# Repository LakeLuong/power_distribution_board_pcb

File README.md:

# power_distribution_board_pcb
Custom KiCad power distribution PCB that takes in +48V and regulates it down to 5V, 3.3V and 12V through two adjustable Lm760660 buck converters and a Tps62913. I made this for a bigger project I am working on for an underwater FPV drone to power different components such as ESCs which will take in +48V, sensors which takes 3.3V and 5V for my raspberry pi, and 12V for cameras. 

BOM: 

Tps62913	Low current buck converter converting 5V to 3.3V	2	$5.52		

Lm70660	High Current Buck Converter that takes 48V and brings it down to 12V and 5V	2	$13.60		

0805 4mOhm resistors	Current-sense resistors	10	$5.57	

0805 54.9k Ohm resistors	resistor connects from RT to AGND, helps with switching frequency	10	$0.37	

0806 20.5kOhm resistors	En Vulo resistors	10	$0.34	

0805 3.24kOhm resistor	Compensation capacitor for lm760660	10	$0.34	

0805 1 Ohm resistor	Bootstrap resistor	10	$0.51

0805 2.49kOhm resistor	feedback divider resistor	10	$0.34	

0805 4.87kOhm resistor	Feedback divider resistor	10	$0.34		

0805 52.3kOhm resistor	S-CONF resistor	10	$0.34	

0805 31.6kOhm resistor	Resistor divider for feedback	10	$0.58	

0805 100kOhm resistor	UVLO resistor, pull up resistors, etc, to control current flow	25	$0.64		

2.2uH inductor	Stores energy during switching and smooths current	3	$6.61	

Ferrite Bead	Blocks high frequency noise	5	$1.55	

0805 470nF Ceramic Capacitor	Reduce low frequency output noise on the Tps62913	10	$1.24	

0806 0.1uF Ceramic Capacitor	High frequency bypass capacitors	10	$1.07

0805 0.1uF Ceramic Capacitor	Decouples VDDA analog bias rail	10	$0.72	

0805 4.7uF Ceramic Capacitor	bypass/decoupling capacitor for VCC	5	$1.60	

0805 22uf Ceramic Capacitor	Smooths output voltage	10	$3.74	

1210 47uF Ceramic Capacitors	Smooths output voltage from regulator	15	$8.42	

0805 10uF Ceramic Capacitors	Input capacitors to provide short bursts of current to regulator	10	$3.48		

1210 4.7 uF Ceramic Capacitors	Input capacitors to provide short burst of current	10	$8.49		

0805 150pf Ceramic Capacitors	Compensation capacitors, helps buck converter stay stable from high frequency noise	10	$0.85		

1210 22uF Ceramic Capacitor	Gives high frequency noise to GND	10	$4.77

0805 10nF Ceramice Capacitors	bypass and filtering + provide positive power supply through VCC	10	$0.60	

0805 0.047 uF Ceramic Capacitor	Boostrap capacitor for buck converter	10	$1.47	

0805 2200pF SMD Ceramic Capacitor	Decoupling and filtering for 5v rail	10	$0.39

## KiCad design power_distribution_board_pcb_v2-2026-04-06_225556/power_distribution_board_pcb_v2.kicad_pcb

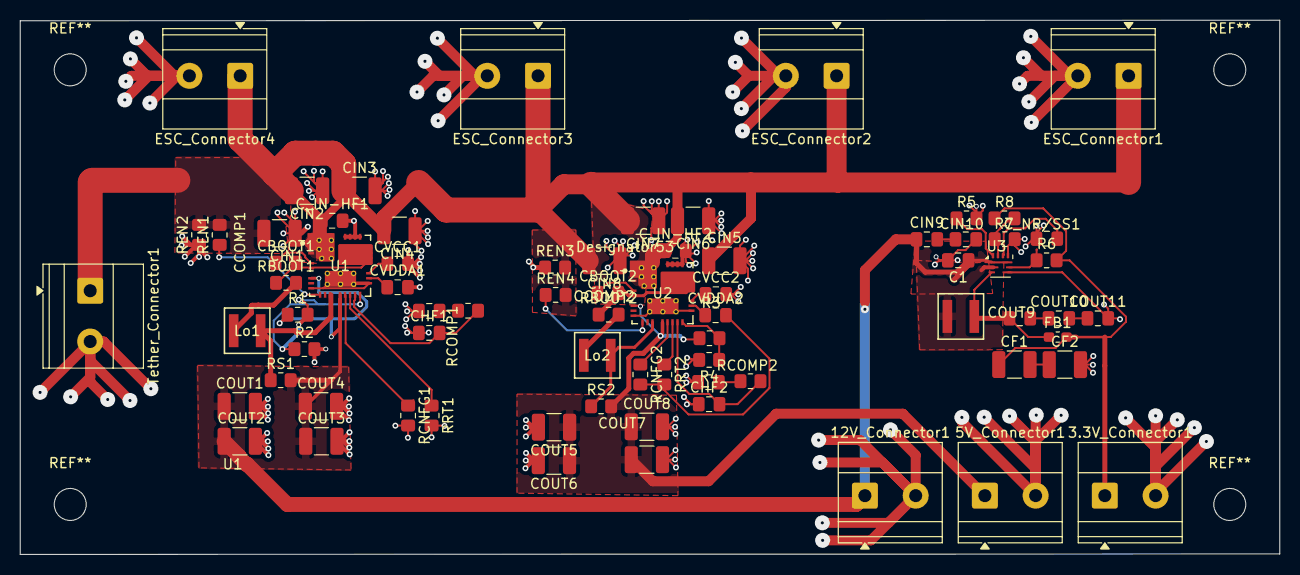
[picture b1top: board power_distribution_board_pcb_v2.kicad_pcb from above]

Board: 2 copper layers, 126.0 x 53.4 mm, 74 parts (0 on the bottom side), 40 nets.

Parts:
3.3V_Connector1, 5V_Connector1, 12V_Connector1: Conn_01x02; TerminalBlock_Phoenix_MKDS-1,5-2-5.08_1x02_P5.08mm_Horizont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
C1: 2.2nF; C_0805_2012Metric_Pad1.18x1.45mm_HandSolder
CBOOT1: 47nF; C_0805_2012Metric_Pad1.18x1.45mm_HandSolder
CBOOT2: 4.7; C_0805_2012Metric_Pad1.18x1.45mm_HandSolder
CCOMP1, CCOMP2: 10nF; C_0805_2012Metric_Pad1.18x1.45mm_HandSolder
CF1, CF2: 22uF; C_1210_3225Metric_Pad1.33x2.70mm_HandSolder
CHF1, CHF2: 150pF; C_0805_2012Metric_Pad1.18x1.45mm_HandSolder
CIN1, CIN2, CIN3, CIN4, CIN5, CIN6, CIN7, CIN8: 4.7µF; C_1210_3225Metric_Pad1.33x2.70mm_HandSolder
CIN9, CIN10: 10uF; C_0805_2012Metric_Pad1.18x1.45mm_HandSolder
COUT1, COUT2, COUT3, COUT4: 47uF; C_1210_3225Metric_Pad1.33x2.70mm_HandSolder
COUT5, COUT6, COUT7, COUT8: 47; C_1210_3225Metric_Pad1.33x2.70mm_HandSolder
COUT9, COUT10, COUT11: 22uF; C_0805_2012Metric_Pad1.18x1.45mm_HandSolder
CVCC1: 4.7uF; C_0805_2012Metric_Pad1.18x1.45mm_HandSolder
CVCC2: 4.7; C_0805_2012Metric_Pad1.18x1.45mm_HandSolder
CVDDA1: 0.1uF; C_0805_2012Metric_Pad1.18x1.45mm_HandSolder
CVDDA2: 0.1; C_0805_2012Metric_Pad1.18x1.45mm_HandSolder
C_IN-HF1, C_IN-HF2: 0.1 µF; C_0805_2012Metric_Pad1.18x1.45mm_HandSolder
C_NR/SS1: 470nF; C_0805_2012Metric_Pad1.18x1.45mm_HandSolder
ESC_Connector1, ESC_Connector2, ESC_Connector3, ESC_Connector4: Conn_01x02; TerminalBlock_Phoenix_MKDS-1,5-2-5.08_1x02_P5.08mm_Horizont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
FB1: FerriteBead; L_0603_1608Metric_Pad1.05x0.95mm_HandSolder
L1: 2.2uH; IND_XGL4030_COC-M
Lo1: 2.2uH; IND_XGL4030_COC-M
Lo2: 3.3; IND_XGL4030_COC-M
R1: 100kF; R_0805_2012Metric_Pad1.20x1.40mm_HandSolder
R2: 31.6kF; R_0805_2012Metric_Pad1.20x1.40mm_HandSolder
R3, R6: 100k; R_0805_2012Metric_Pad1.20x1.40mm_HandSolder
R4: 31.6k; R_0805_2012Metric_Pad1.20x1.40mm_HandSolder
R5: 52.3k; R_0805_2012Metric_Pad1.20x1.40mm_HandSolder
R7: 4.87k; R_0805_2012Metric_Pad1.20x1.40mm_HandSolder
R8: 2.49k; R_0805_2012Metric_Pad1.20x1.40mm_HandSolder
RBOOT1, RBOOT2: 1Ohm; R_0805_2012Metric_Pad1.20x1.40mm_HandSolder
RCNFG1, RCNFG2: 29.4K; R_0805_2012Metric_Pad1.20x1.40mm_HandSolder
RCOMP1: 3.24kF; R_0805_2012Metric_Pad1.20x1.40mm_HandSolder
RCOMP2: 3.24k; R_0805_2012Metric_Pad1.20x1.40mm_HandSolder
REN1, REN4: 100k; R_0805_2012Metric_Pad1.20x1.40mm_HandSolder
REN2, REN3: 20.5k; R_0805_2012Metric_Pad1.20x1.40mm_HandSolder
RRT1: 54.9K; R_0805_2012Metric_Pad1.20x1.40mm_HandSolder
RRT2: R; R_0805_2012Metric_Pad1.20x1.40mm_HandSolder
RS1: 4mQ; R_0805_2012Metric_Pad1.20x1.40mm_HandSolder
RS2: 5m; R_0805_2012Metric_Pad1.20x1.40mm_HandSolder
Tether_Connector1: Conn_01x02; TerminalBlock_Phoenix_MKDS-1,5-2-5.08_1x02_P5.08mm_Horizont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
U1, U2: LM70660RRXR; RRX0029B-MFG
U3: TPS62913; Texas_RPU0010A_VQFN-HR-10_2x2mm_P0.5mm

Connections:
+48V: CIN1.2, CIN2.2, CIN3.1, CIN4.2, CIN5.1, CIN6.2, CIN7.2, CIN8.2, C_IN-HF1.1, C_IN-HF2.1, ESC_Connector1.1, ESC_Connector2.1, ESC_Connector3.1, ESC_Connector4.1, REN1.2, REN2.2, REN3.2, REN4.2, Tether_Connector1.1, U1.1 (VIN4), U1.2 (VIN5), U1.3 (VIN6), U1.27 (VIN1), U1.28 (VIN2), U1.29 (VIN3), U1.37, U1.38, U1.39, U1.40, U1.41, U1.42, U2.1 (VIN4), U2.2 (VIN5), U2.3 (VIN6), U2.27 (VIN1), U2.28 (VIN2), U2.29 (VIN3), U2.37, U2.38, U2.39, U2.40, U2.41
/3.3V_BUS: 3.3V_Connector1.1, CF1.1, FB1.2, R6.2, R8.1
/5V_BUS: 5V_Connector1.1, COUT5.1, COUT6.1, COUT7.1, COUT8.1, R3.1, RS2.2, U2.6 (BIAS), U2.12 (VOUT)
/12V_BUS: 12V_Connector1.1, C1.1, CIN9.1, COUT1.1, COUT2.1, COUT3.1, COUT4.1, R1.1, RS1.2, U1.6 (BIAS), U1.12 (VOUT), U3.1 (EN/SYNC), U3.6 (VIN)
/AGND: CVDDA2.2, RCNFG2.2, RRT2.2
/CONFIG: RCNFG2.1, U2.13 (CONFIG)
/CONFIG_12V: RCNFG1.1, U1.13 (CONFIG)
/EN_UVLO: REN4.1, U2.9 (EN_UVLO)
/EN_UVLO_12V: REN1.1, U1.9 (EN_UVLO)
/EXTCOMP: CHF2.2, RCOMP2.2, U2.15 (EXTCOMP)
/EXTCOMP_12V: CHF1.2, RCOMP1.2, U1.15 (EXTCOMP)
/FB_5V: R3.2, R4.1, U2.16 (FB)
/FB_12V: R1.2, R2.1, U1.16 (FB)
/NR/SS: C_NR/SS1.2, U3.8 (NR/SS)
/RT: RRT2.1, U2.14 (RT)
/RT_12V: RRT1.1, U1.14 (RT)
/VDDA: CVDDA2.1, U2.18 (VDDA)
/VDDA_12V: CVDDA1.1, U1.18 (VDDA)
GND: 3.3V_Connector1.2, 5V_Connector1.2, 12V_Connector1.2, C1.2, CCOMP1.1, CCOMP2.1, CF2.2, CHF1.1, CHF2.1, CIN1.1, CIN2.1, CIN3.2, CIN4.1, CIN5.2, CIN6.1, CIN7.1, CIN8.1, CIN10.2, COUT1.2, COUT2.2, COUT3.2, COUT4.2, COUT5.2, COUT6.2, COUT7.2, COUT8.2, COUT11.2, CVCC1.2, CVCC2.2, CVDDA1.2, C_IN-HF1.2, C_IN-HF2.2, C_NR/SS1.1, ESC_Connector1.2, ESC_Connector2.2, ESC_Connector3.2, ESC_Connector4.2, R2.2, R4.2, R5.2, R7.2, RCNFG1.2, REN2.1, REN3.1, RRT1.2, Tether_Connector1.2, U1.8 (PFM_SYNCIN), U1.17 (AGND), U1.23 (PGND1), U1.24 (PGND2), U1.25 (PGND3), U1.26 (PGND4), U1.30 (PGND), U1.31, U1.32, U1.33, U1.34, U1.35, U1.36, U2.8 (PFM_SYNCIN), U2.17 (AGND), U2.23 (PGND1), U2.24 (PGND2), U2.25 (PGND3), U2.26 (PGND4), U2.30 (PGND), U2.31, U2.32, U2.33, U2.34, U2.35, U2.36, U3.4 (PGND), U3.7 (PSNS)
unnamed: CCOMP1.2, RCOMP1.1
unnamed: CCOMP2.2, RCOMP2.1
unnamed: CF1.2, CF2.1
unnamed: CIN9.2, CIN10.1
unnamed: COUT9.2, COUT10.1
unnamed: COUT10.2, COUT11.1
unnamed: Lo1.1, RBOOT1.2
unnamed: Lo2.1, RBOOT2.2
unnamed: CBOOT1.1, U1.4 (CBOOT)
unnamed: Lo1.2, RS1.1, U1.11 (ISNS+)
unnamed: CBOOT1.2, RBOOT1.1, U1.5 (SW4), U1.20 (SW1), U1.21 (SW2), U1.22 (SW3)
unnamed: CVCC1.1, U1.19 (VCC)
unnamed: CBOOT2.1, U2.4 (CBOOT)
unnamed: Lo2.2, RS2.1, U2.11 (ISNS+)
unnamed: CBOOT2.2, RBOOT2.1, U2.5 (SW4), U2.20 (SW1), U2.21 (SW2), U2.22 (SW3)
unnamed: CVCC2.1, U2.19 (VCC)
unnamed: R7.1, R8.2, U3.9 (FB)
unnamed: R6.1, U3.5 (PG)
unnamed: R5.1, U3.10 (S-CONF)
unnamed: L1.1, U3.2 (SW)
unnamed: COUT9.1, FB1.1, L1.2, U3.3 (VO)

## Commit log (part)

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2026-03-28 Added buck converter datasheet
2026-03-30 Added new datasheet for low noise voltage regulator
2026-04-01 added schematic and footprint
2026-04-03 Added project files
2026-04-07 Added version 2 of the pcb schematic
2026-06-03 Update KiCad project files
2026-06-03 moved files
2026-06-03 Revise README description for power distribution PCB
    Updated project description to specify input voltage and output regulation details.
2026-06-03 Update README with project application details
    Expanded project description to include application details for underwater FPV drone.
2026-06-03 Update README with project image
    Added an image to the README for better visualization.
2026-06-03 Add an image to README for enhanced documentation
    Added an additional image to the README for better visualization.
2026-06-04 Added step file
2026-06-04 Update README with component specifications and costs and BOM
    Added detailed component list with descriptions and pricing.
2026-06-04 Fix BOM formatting in README.md
2026-06-04 Move STEP file into CAD folder
2026-06-17 update pcb and schematic
